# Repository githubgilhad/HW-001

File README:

HW deska pro CPU+RAM+GLUE+SystemBus - prvni navrh

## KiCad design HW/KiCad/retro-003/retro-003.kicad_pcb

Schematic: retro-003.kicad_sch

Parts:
C1, C2: 20p; C_Disc_D5.0mm_W2.5mm_P2.50mm
C12: 100n RESET; C_Disc_D3.0mm_W2.0mm_P2.50mm
Cx6, Cx7, Cx8, Cx9, Cx10, Cx11, Cx12, Cx13, Cx16, Cx17, Cx18: Cx; C_Disc_D3.0mm_W2.0mm_P2.50mm
Cx14, Cx15, Cx27, Cx28: Cx; CP_Radial_D5.0mm_P2.50mm
Cx19, Cx20, Cx21, Cx22, Cx23, Cx24, Cx25, Cx26: 10p; C_Disc_D3.0mm_W2.0mm_P2.50mm
D2: D; D_1210_3225Metric_HandSolder
H5, H6, H7, H8: MountingHole; MountingHole_3.2mm_M3_Pad
J1: ATF_JTAG; IDC-Header_2x05_P2.54mm_Vertical
J2: Conn_02x04_Top_Bottom; PinSocket_2x04_P2.54mm_Vertical
J3: Serial; PinHeader_1x04_P2.54mm_Vertical
J4: SysBus; PinSocket_2x32_P2.54mm_Vertical
J5, J8, J21, J22, J37, J38, J39, J40, J41, J42, J43, J44, J45, J46, J47, J48, J49, J50, J51, J52, J53, J54, J55, J56, J57, J58, J59, J60, J61, J62, J63, J64, J65, J66, J67, J68, J69, J70, J71, J72, J73, J74, J75, J76, J77, J78, J79, J80, J81, J82, J83, J84, J85, J86, J87, J88, J89, J90, J91, J92, J93, J94, J95, J96, J97, J98, J99, J100, J101, J102, J103, J104, J105, J106: x; PinHole_1x01_2.54xrectangle
J6: SysBus; PinHeader_2x32_P2.54mm_Vertical_down
J7: Conn_01x16_Pin; G_SOIC-16_3.9x9.9mm_HandSolder
J12: Reset; PinHole_1x01_2.54xrectangle
JP1: Nx4; SolderJumper-2_P1.3mm_Bridged_Pad1.0x1.5mm
JP2: Nx5; SolderJumper-2_P1.3mm_Bridged_Pad1.0x1.5mm
JP3: Nx6; SolderJumper-2_P1.3mm_Bridged_Pad1.0x1.5mm
JP4: Nx1; SolderJumper-2_P1.3mm_Bridged_Pad1.0x1.5mm
JP5: Nx2; SolderJumper-2_P1.3mm_Bridged_Pad1.0x1.5mm
JP13: Nx3; SolderJumper-2_P1.3mm_Bridged_Pad1.0x1.5mm
Jx1: BugFix; PinHeader_1x03_P2.54mm_Vertical
Jx2: BootFrom; PinHeader_1x03_P2.54mm_Vertical
Jx4: J; PinHeader_1x08_P2.54mm_Vertical
L0: LReset; LED_0805_2012Metric
L1: LHALT; LED_0805_2012Metric
L2: A_HALT; LED_0805_2012Metric
L3: ROM; LED_0805_2012Metric
L4: LRomMapped; LED_0805_2012Metric
L5: B_HALT; LED_0805_2012Metric
L6: MHF_B; LED_0805_2012Metric
L7: MHF_A; LED_0805_2012Metric
L8: RAM; LED_0805_2012Metric
L9: Dev_3; LED_0805_2012Metric
L10: ACIA; LED_0805_2012Metric
L11: VIA; LED_0805_2012Metric
L12: Dev_6; LED_0805_2012Metric
L13: Dev_5; LED_0805_2012Metric
L14: Dev_4; LED_0805_2012Metric
L17: Dev_7; LED_0805_2012Metric
L36: A0; LED_0805_2012Metric
L37, L57: A1; LED_0805_2012Metric
L38, L56: A2; LED_0805_2012Metric
L39: A3; LED_0805_2012Metric
L40: A4; LED_0805_2012Metric
L41: A5; LED_0805_2012Metric
L42: A6; LED_0805_2012Metric
L43: A7; LED_0805_2012Metric
L44: B0; LED_0805_2012Metric
L45, L55: B1; LED_0805_2012Metric
L46, L54: B2; LED_0805_2012Metric
L47: B3; LED_0805_2012Metric
L48: B4; LED_0805_2012Metric
L49: B5; LED_0805_2012Metric
L50: B6; LED_0805_2012Metric
L51: B7; LED_0805_2012Metric
L52: IA; LED_0805_2012Metric
L53: IB; LED_0805_2012Metric
L58: Rx; LED_0805_2012Metric
L59: Tx; LED_0805_2012Metric
LS1: Speaker_Crystal; Buzzer_12x9.5RM7.6
LSys1: Sys; LED_0805_2012Metric
M3: CY7C109D-10ZXI; G_TSOP-I-32_18.4x8mm_HandSolder
PA1: J; PinHeader_1x10_P2.54mm_Vertical
PB1: J; PinHeader_1x10_P2.54mm_Vertical
Q1: MMBT3904; SOT-23
R0, R1, R2, R3, R4, R5, R6, R7, R8, R9, R10, R11, R12, R13, R14, R17, R61, R62, R69, R70, R71, R72, R73, R74, R75, R76, R77, R78, R79, R80, R81, R82, R83, R84, R85, R86, R87, R88, R89, R90, R91, R92: 1k; R_0805_2012Metric_Pad1.20x1.40mm_HandSolder
R36, R37, R38, R39, R44, R45, R46, R47: 5k8; R_0805_2012Metric
R40, R41, R42, R43: 220; R_0805_2012Metric
R48, R49, R50, R51, R52, R53, R54, R55, R56, R57, R58, R59, R64, R95, R96, R98, R99, R100, R102: 10k; R_0805_2012Metric_Pad1.20x1.40mm_HandSolder
R60: 1M; R_0805_2012Metric_Pad1.20x1.40mm_HandSolder
R63: 3k3; R_0805_2012Metric_Pad1.20x1.40mm_HandSolder
R93, R94: 50k; R_0805_2012Metric_Pad1.20x1.40mm_HandSolder
S1: Reset; G_Arduino_switch; PARTREV 1.0
TP1, TP16: 7; TestPoint_Pad_1.0x1.0mm
TP2, TP9: 0; TestPoint_Pad_1.0x1.0mm
TP3, TP10: 1; TestPoint_Pad_1.0x1.0mm
TP4, TP11: 2; TestPoint_Pad_1.0x1.0mm
TP5, TP12: 3; TestPoint_Pad_1.0x1.0mm
TP6, TP13: 4; TestPoint_Pad_1.0x1.0mm
TP7, TP14: 5; TestPoint_Pad_1.0x1.0mm
TP8, TP15: 6; TestPoint_Pad_1.0x1.0mm
TP17: D; TestPoint_Pad_1.0x1.0mm
TP18: Clk; TestPoint_Pad_1.0x1.0mm
TP19, TP36: Q; TestPoint_Pad_1.0x1.0mm
TP20: ~{Q}; TestPoint_Pad_1.0x1.0mm
TP21: ~{R}; TestPoint_Pad_1.0x1.0mm
TP22: ~{S}; TestPoint_Pad_1.0x1.0mm
TP23: N3; TestPoint_Pad_1.0x1.0mm
TP24: N4; TestPoint_Pad_1.0x1.0mm
TP25: N5; TestPoint_Pad_1.0x1.0mm
TP26: N6; TestPoint_Pad_1.0x1.0mm
TP27: ~{N3}; TestPoint_Pad_1.0x1.0mm
TP28: ~{N4}; TestPoint_Pad_1.0x1.0mm
TP29: ~{N5}; TestPoint_Pad_1.0x1.0mm
TP30: ~{N6}; TestPoint_Pad_1.0x1.0mm
TP31: DEV7; TestPoint_Pad_1.0x1.0mm
TP32: DMA; TestPoint_Pad_1.0x1.0mm
TP33: MRDY; TestPoint_Pad_1.0x1.0mm
TP34: BA; TestPoint_Pad_1.0x1.0mm
TP35: BS; TestPoint_Pad_1.0x1.0mm
TP37: N1; TestPoint_Pad_1.0x1.0mm
TP38: N2; TestPoint_Pad_1.0x1.0mm
TP39: ~{N1}; TestPoint_Pad_1.0x1.0mm
TP40: ~{N2}; TestPoint_Pad_1.0x1.0mm
U1: HD6309; DIP-40_W15.24mm
U4: MC68B50; DIP-24_W15.24mm
U5: 6822; DIP-40_W15.24mm
U6, U7, U8: 74HC14; SOIC-14_3.9x8.7mm_P1.27mm
U12: 74HC04; SOIC-14_3.9x8.7mm_P1.27mm
U13: 74HC74; SOIC-14_3.9x8.7mm_P1.27mm
U14: 28C256; DIP-28_W15.24mm
U15: ATF1508AS-10AU100; ATF1508-AS_TQFP100_long
XTAL1: 16MHz; Crystal_HC49-4H_Vertical
Y1: 1.8432 MHz; Crystal_THT_15_5mm

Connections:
+5V: Cx6.1, Cx7.1, Cx8.1, Cx9.1, Cx10.1, Cx11.1, Cx12.1, Cx13.1, Cx14.1, Cx15.1, Cx16.1, Cx17.1, Cx18.1, Cx27.1, Cx28.1, D2.1 (K), J1.4 (Vcc), J2.1, J2.3, J2.5, J2.7, J3.4, J4.1, J4.2, J5.1, J6.1, J6.2, Jx4.8, L6.2 (A), L7.2 (A), LS1.1, LSys1.2 (A), M3.6 (CS2/CE2), M3.8 (VCC), PA1.10, PB1.10, R36.2, R37.2, R38.2, R39.2, R48.2, R49.2, R50.2, R51.2, R52.2, R53.2, R54.2, R55.2, R56.2, R57.2, R58.2, R59.2, R63.1, R64.1, R93.1, R94.1, R95.2, R98.2, R99.2, R100.2, R102.2, U1.7 (VCC), U4.8 (CS0), U4.10 (CS1), U4.12 (VCC), U5.20 (VCC), U5.22 (CS0), U5.24 (CS1), U6.14 (VCC), U7.14 (VCC), U8.14 (VCC), U12.14 (VCC), U13.1 (~R), U13.4 (~S), U13.14 (VCC), U14.28 (VCC), U15.3 (VCCIO), U15.18 (VCCIO), U15.34 (VCCIO), U15.39 (VCCINT), U15.51 (VCCIO), U15.66 (VCCIO), U15.82 (VCCIO), U15.91 (VCCINT)
/A_HALT: J4.29, J6.29, R93.2, U6.1, U15.27 (I/O)
/A_SHARE_DIRTY: J4.33, J6.33, U15.31 (I/O)
/A_SHARE_REQUEST: J4.37, J6.37, U15.36 (I/O)
/A_S_16: J4.27, J6.27, R100.1, U15.24 (I/O)
/B_READ: J4.32, J6.32, U15.30 (I/O)
/B_SHARE_DIRTY: J4.34, J6.34, U15.32 (I/O)
/B_SHARE_REQUEST: J4.38, J6.38, U15.37 (I/O)
/B_SHARE_SELECT: J4.52, J6.52, U15.55 (I/O)
/B_S_16: J4.28, J6.28, R102.1, U15.25 (I/O)
/BootSrc: Jx2.2, U15.84 (I/O)
/CA0: J4.11, J6.11, M3.20 (A0), U1.8 (A0), U4.11 (RS), U5.36 (RS0), U14.10 (A0), U15.5 (I/O)
/CA1: J4.12, J6.12, M3.19 (A1), U1.9 (A1), U5.35 (RS1), U14.9 (A1), U15.6 (I/O)
/CA2: J4.13, J6.13, M3.18 (A2), U1.10 (A2), U14.8 (A2), U15.7 (I/O)
/CA3: J4.14, J6.14, M3.17 (A3), U1.11 (A3), U14.7 (A3), U15.8 (I/O)
/CA4: J4.15, J6.15, M3.16 (A4), U1.12 (A4), U14.6 (A4), U15.9 (I/O)
/CA5: J4.16, J6.16, M3.15 (A5), U1.13 (A5), U14.5 (A5), U15.10 (I/O)
/CA6: J4.17, J6.17, M3.14 (A6), U1.14 (A6), U14.4 (A6), U15.12 (I/O)
/CA7: J4.18, J6.18, M3.13 (A7), U1.15 (A7), U14.3 (A7), U15.13 (I/O)
/CA8: J4.19, J6.19, M3.3 (A8), U1.16 (A8), U14.25 (A8), U15.14 (I/O)
/CA9: J4.20, J6.20, M3.2 (A9), U1.17 (A9), U14.24 (A9), U15.16 (I/O)
/CA10: J4.21, J6.21, M3.31 (A10), U1.18 (A10), U14.21 (A10), U15.17 (I/O)
/CA11: J4.22, J6.22, M3.1 (A11), U1.19 (A11), U14.23 (A11), U15.19 (I/O)
/E: J4.53, J6.53, U1.34 (E), U4.14 (E), U5.25 (ENABLE), U13.3 (C), U15.87 (INPUT/GCLK1)
/GA12: J4.23, J6.23, M3.12 (A12), U14.2 (A12), U15.61 (I/O)
/GA13: J4.24, J6.24, M3.4 (A13), U14.26 (A13), U15.60 (I/O)
/GA14: J4.25, J6.25, M3.11 (A14), U14.1 (A14), U15.58 (I/O)
/GA15: J4.26, J6.26, M3.7 (A15), U15.57 (I/O)
/RomMapped: U6.11, U15.85 (I/O/GCLK3)
/Rx: J3.1, R91.2, U4.2 (Rx_Data)
/R~W: J4.54, J6.54, U1.32 (R/~W), U4.13 (R/~W), U5.21 (R/~W), U15.93 (I/O)
/Tx: J3.2, R92.2, U4.6 (Tx_Data)
/mA_READ: J4.31, J6.31, U15.29 (I/O)
/mA_SHARE_GRANTED: J4.35, J6.35, U7.3, U15.33 (I/O)
/mA_SHARE_SELECT: J4.51, J6.51, U15.54 (I/O)
/mB_HALT: J4.30, J6.30, R94.2, U6.13, U15.28 (I/O)
/mB_SHARE_GRANTED: J4.36, J6.36, U7.1, U15.35 (I/O)
/vCA1: Jx4.1, R90.2, U5.40 (CA1)
/vCA2: Jx4.2, R89.2, U5.39 (CA2)
/vCB1: Jx1.1, Jx4.3, R88.2, U13.2 (D)
/vCB2: Jx4.4, R87.2, U5.19 (CB2)
/v~IRQA: Jx4.5, R86.2, U5.38 (~IRQA)
/v~IRQB: Jx4.6, R85.2, U5.37 (~IRQB)
/~Dev_1: J4.58, J6.58, R55.1, U7.9, U15.70 (I/O)
/~Dev_2: J4.59, J6.59, R56.1, U8.5, U15.71 (I/O)
/~Dev_3: J4.60, J6.60, R57.1, U8.3, U15.72 (I/O)
/~Dev_4: J4.61, J6.61, R58.1, U8.1, U15.75 (I/O)
/~FIRQ: J4.57, J6.57, R50.1, U1.4 (~FIRQ), U15.80 (I/O)
/~IRQ: J4.56, J6.56, R49.1, U1.3 (~IRQ), U4.7 (~IRQ), U15.81 (I/O)
/~NMI: J4.55, J6.55, R48.1, U1.2 (~NMI), U15.83 (I/O)
ACIA Clk 1.8432 MHz: U4.3 (Rx_CLK), U4.4 (Tx_CLK), U12.4
A_G_A_DIR: J4.47, J6.47, U15.49 (I/O)
A_G_D_DIR: J4.49, J6.49, U15.52 (I/O)
A_G_ENABLE: J4.45, J6.45, U15.47 (I/O)
A_S_READ: J4.41, J6.41, U15.42 (I/O)
A_S_SELECT: J4.39, J6.39, U15.40 (I/O)
A_S_WRITE: J4.43, J6.43, U15.45 (I/O)
BA: TP34.1, U1.6 (BA), U15.88 (12V/INPUT/OE1)
BS: TP35.1, U1.5 (BS), U15.77 (I/O)
B_G_A_DIR: J4.48, J6.48, U15.50 (I/O)
B_G_D_DIR: J4.50, J6.50, U15.53 (I/O)
B_G_ENABLE: J4.46, J6.46, U15.48 (I/O)
B_S_READ: J4.42, J6.42, U15.44 (I/O)
B_S_SELECT: J4.40, J6.40, U15.41 (I/O/PD2)
B_S_WRITE: J4.44, J6.44, U15.46 (I/O)
CA12: U1.20 (A12), U15.20 (I/O)
CA13: U1.21 (A13), U15.21 (I/O)
CA14: U1.22 (A14), U15.22 (I/O)
CA15: U1.23 (A15), U15.23 (I/O)
D0: J4.3, J6.3, M3.21 (DQ0), U1.31 (D0), U4.22 (D0), U5.33 (D0), U14.11 (D0), U15.94 (I/O)
D1: J4.4, J6.4, M3.22 (DQ1), U1.30 (D1), U4.21 (D1), U5.32 (D1), U14.12 (D1), U15.96 (I/O)
D2: J4.5, J6.5, M3.23 (DQ2), U1.29 (D2), U4.20 (D2), U5.31 (D2), U14.13 (D2), U15.97 (I/O)
D3: J4.6, J6.6, M3.25 (DQ3), U1.28 (D3), U4.19 (D3), U5.30 (D3), U14.15 (D3), U15.98 (I/O)
D4: J4.7, J6.7, M3.26 (DQ4), U1.27 (D4), U4.18 (D4), U5.29 (D4), U14.16 (D4), U15.99 (I/O)
D5: J4.8, J6.8, M3.27 (DQ5), U1.26 (D5), U4.17 (D5), U5.28 (D5), U14.17 (D5), U15.100 (I/O)
D6: J4.9, J6.9, M3.28 (DQ6), U1.25 (D6), U4.16 (D6), U5.27 (D6), U14.18 (D6), U15.1 (PD1/I/O)
D7: J4.10, J6.10, M3.29 (DQ7), U1.24 (D7), U4.15 (D7), U5.26 (D7), U14.19 (D7), U15.2 (I/O)
GA16: M3.10 (A16), U15.56 (I/O)
GND: C1.1, C2.1, C12.2, Cx6.2, Cx7.2, Cx8.2, Cx9.2, Cx10.2, Cx11.2, Cx12.2, Cx13.2, Cx14.2, Cx15.2, Cx16.2, Cx17.2, Cx18.2, Cx19.2, Cx20.2, Cx21.2, Cx22.2, Cx23.2, Cx24.2, Cx25.2, Cx26.2, Cx27.2, Cx28.2, J1.2 (GND), J1.10 (GND), J2.2, J2.4, J2.6, J2.8, J3.3, J4.63, J4.64, J6.63, J6.64, J8.1, JP1.1 (A), JP2.1 (A), JP3.1 (A), JP4.1 (A), JP5.1 (A), JP13.1 (A), Jx4.7, L0.1 (K), L1.1 (K), L2.1 (K), L3.1 (K), L4.1 (K), L5.1 (K), L8.1 (K), L9.1 (K), L10.1 (K), L11.1 (K), L12.1 (K), L13.1 (K), L14.1 (K), L17.1 (K), L36.1 (K), L37.1 (K), L38.1 (K), L39.1 (K), L40.1 (K), L41.1 (K), L42.1 (K), L43.1 (K), L44.1 (K), L45.1 (K), L46.1 (K), L47.1 (K), L48.1 (K), L49.1 (K), L50.1 (K), L51.1 (K), L52.1 (K), L53.1 (K), L54.1 (K), L55.1 (K), L56.1 (K), L57.1 (K), L58.1 (K), L59.1 (K), M3.24 (GND), PA1.9, PB1.9, Q1.2 (E), R44.1, R45.1, R46.1, R47.1, R62.1, R96.2, S1.3 (K), S1.4 (A), U1.1 (VSS), U4.1 (VSS), U4.23 (~DCD), U4.24 (~CTS), U5.1 (VSS), U6.7 (GND), U7.7 (GND), U8.7 (GND), U12.7 (GND), U13.7 (GND), U14.14 (GND), U15.11 (GND), U15.26 (GND), U15.38 (GND), U15.43 (GND), U15.59 (GND), U15.74 (GND), U15.86 (GND), U15.95 (GND)
JT_TCK: R36.1, R40.1, R44.2, U15.62 (I/O/TCK)
JT_TDI: R39.1, R43.1, R47.2, U15.4 (I/O/TDI)
JT_TDO: R37.1, R41.1, R45.2, U15.73 (I/O/TDO)
JT_TMS: R38.1, R42.1, R46.2, U15.15 (I/O/TMS)
MRDY: R52.1, TP33.1, U1.36 (MRDY), U15.78 (I/O)
MasterReset: C12.1, D2.2 (A), J4.62, J6.62, J12.1, R64.2, S1.1, S1.2, U1.37 (~RESET), U5.34 (~RESET), U6.5, U15.89 (INPUT/GCLR)
unnamed: Cx19.1, Cx20.1, Cx21.1, Cx22.1, R60.1, U12.2, U12.3, Y1.2
unnamed: Cx23.1, Cx24.1, Cx25.1, Cx26.1, R60.2, U12.1, Y1.1
unnamed: J1.1 (TCK), R40.2
unnamed: J1.9 (TDI), R43.2
unnamed: J1.3 (TDO), R41.2
unnamed: J1.5 (TMS), R42.2
unnamed: J7.1, TP2.1
unnamed: J7.2, TP3.1
unnamed: J7.3, TP4.1
unnamed: J7.4, TP5.1
unnamed: J7.5, TP6.1
unnamed: J7.6, TP7.1
unnamed: J7.7, TP8.1
unnamed: J7.8, TP1.1
unnamed: J7.9, TP16.1
unnamed: J7.10, TP15.1
unnamed: J7.11, TP14.1
unnamed: J7.12, TP13.1
unnamed: J7.13, TP12.1
unnamed: J7.14, TP11.1
unnamed: J7.15, TP10.1
unnamed: J7.16, TP9.1
unnamed: JP1.2 (B), TP24.1, U12.9
unnamed: JP2.2 (B), TP25.1, U12.11
unnamed: JP3.2 (B), TP26.1, U12.13
unnamed: JP4.2 (B), TP37.1, U8.11
unnamed: JP5.2 (B), TP38.1, U8.9
unnamed: JP13.2 (B), TP23.1, U12.5
unnamed: Jx1.2, U5.18 (CB1)
unnamed: Jx1.3, U13.5 (Q)
unnamed: Jx2.1, R95.1
unnamed: Jx2.3, R96.1
unnamed: L0.2 (A), R1.1
unnamed: L1.2 (A), R2.1
unnamed: L2.2 (A), R0.1
unnamed: L3.2 (A), R3.1
unnamed: L4.2 (A), R4.1
unnamed: L5.2 (A), R5.1
unnamed: L6.1 (K), R6.1
unnamed: L7.1 (K), R7.1
unnamed: L8.2 (A), R8.1
unnamed: L9.2 (A), R9.1
unnamed: L10.2 (A), R10.1
unnamed: L11.2 (A), R11.1
unnamed: L12.2 (A), R12.1
unnamed: L13.2 (A), R13.1
unnamed: L14.2 (A), R14.1
unnamed: L17.2 (A), R17.1
unnamed: L36.2 (A), R69.1
unnamed: L37.2 (A), R70.1
unnamed: L38.2 (A), R71.1
unnamed: L39.2 (A), R72.1
unnamed: L40.2 (A), R73.1
unnamed: L41.2 (A), R74.1
unnamed: L42.2 (A), R75.1
unnamed: L43.2 (A), R76.1
unnamed: L44.2 (A), R77.1
unnamed: L45.2 (A), R78.1
unnamed: L46.2 (A), R79.1
unnamed: L47.2 (A), R80.1
unnamed: L48.2 (A), R81.1
unnamed: L49.2 (A), R82.1
unnamed: L50.2 (A), R83.1
unnamed: L51.2 (A), R84.1
unnamed: L52.2 (A), R85.1
unnamed: L53.2 (A), R86.1
unnamed: L54.2 (A), R87.1
unnamed: L55.2 (A), R88.1
unnamed: L56.2 (A), R89.1
unnamed: L57.2 (A), R90.1
unnamed: L58.2 (A), R91.1
unnamed: L59.2 (A), R92.1
unnamed: LSys1.1 (K), R62.2
unnamed: PA1.1, R69.2, U5.2 (PA0)
unnamed: PA1.2, R70.2, U5.3 (PA1)
unnamed: PA1.3, R71.2, U5.4 (PA2)
unnamed: PA1.4, R72.2, U5.5 (PA3)
unnamed: PA1.5, R73.2, U5.6 (PA4)
unnamed: PA1.6, R74.2, U5.7 (PA5)
unnamed: PA1.7, R75.2, U5.8 (PA6)
unnamed: PA1.8, R76.2, U5.9 (PA7)
unnamed: PB1.1, R77.2, U5.10 (PB0)
unnamed: PB1.2, R78.2, U5.11 (PB1)
unnamed: PB1.3, R79.2, U5.12 (PB2)
unnamed: PB1.4, R80.2, U5.13 (PB3)
unnamed: PB1.5, R81.2, U5.14 (PB4)
unnamed: PB1.6, R82.2, U5.15 (PB5)
unnamed: PB1.7, R83.2, U5.16 (PB6)
unnamed: PB1.8, R61.1, R84.2, U5.17 (PB7)
unnamed: Q1.1 (B), R61.2
unnamed: LS1.2, Q1.3 (C)
unnamed: R0.2, U6.2
unnamed: R1.2, U6.6
unnamed: R2.2, U6.4
unnamed: R3.2, U6.8
unnamed: R4.2, U6.10
unnamed: R5.2, U6.12
unnamed: R6.2, U7.2
unnamed: R7.2, U7.4
unnamed: R8.2, U7.6
unnamed: R9.2, U7.8
unnamed: R10.2, U7.10
unnamed: R11.2, U7.12
unnamed: R12.2, U8.2
unnamed: R13.2, U8.4
unnamed: R14.2, U8.6
unnamed: R17.2, U8.12
unnamed: TP27.1, U12.6
unnamed: TP28.1, U12.8
unnamed: TP29.1, U12.10
unnamed: TP30.1, U12.12
unnamed: TP39.1, U8.10
unnamed: TP40.1, U8.8
unnamed: C2.2, U1.38 (EXTAL), XTAL1.2
unnamed: C1.2, U1.39 (XTAL), XTAL1.1
unnamed: TP18.1, U13.11 (C)
unnamed: TP17.1, U13.12 (D)
unnamed: TP19.1, U13.9 (Q)
unnamed: TP20.1, U13.8 (~Q)
unnamed: TP21.1, U13.13 (~R)
unnamed: TP22.1, U13.10 (~S)
Q: TP36.1, U1.35 (Q), U15.90 (INPUT/OE2/GCLK2)
~DMA/BREQ: R51.1, TP32.1, U1.33 (~DMA/BREQ), U15.79 (I/O)
~Dev_Sel_1: R53.1, U5.23 (~CS2), U7.13, U15.68 (I/O)
~Dev_Sel_2: R54.1, U4.9 (CS2), U7.11, U15.69 (I/O)
~Dev_Sel_7: R59.1, TP31.1, U8.13, U15.76 (I/O)
~HALT: R63.2, U1.40 (~HALT), U6.3, U15.92 (I/O)
~RAM: M3.30 (~CS1/~CE1), R98.1, U7.5, U15.67 (I/O)
~ROM: R99.1, U6.9, U14.20 (~CS), U15.65 (I/O)
~Read: M3.32 (~OE), U14.22 (~OE), U15.63 (I/O)
~Write: M3.5 (~WE), U14.27 (~WE), U15.64 (I/O)

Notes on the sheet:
~Reset, NMI, IRQ, FIRQ,E,R~{W}
OUT
Dev_0 RAM
5 E, R/~W ~Reset, HALT, BA
I2C style pullup
60+2+2
Dev 0
RAM
PULLUPS
ATF - 1
Dev_Sel_0 = RAM Dev_Sel_1 = OnBoard VIA Dev_Sel_2 = OnBoard ACIA Dev_Sel_3 = Bus_1 Dev_Sel_4 = Bus_2 Dev_Sel_5 = Bus_3 Dev_Sel_6 = Bus_4 Dev_Sel_7 = OnBoard future use
2x MHF-002
Dev X
TESTPOINTS
SYSTEM LEDs
For future use maybe
CONFIG
HD6309
A000..A01F
EMS2 4K
A100..FFFF
RANGE
TYP
Native RAM 32K
9000..9FFF
0001
6 GLUE registers (xxx = regnum)
0000
1xxx
0100
Memory mapped devices (? 15 x 16 B?)
0011
6309 memory regions
EMS1 4K
A020..A0FF
Native RAM ~ ROM 23.75K
0000..7FFF
CONTENT
0010
8000..8FFF

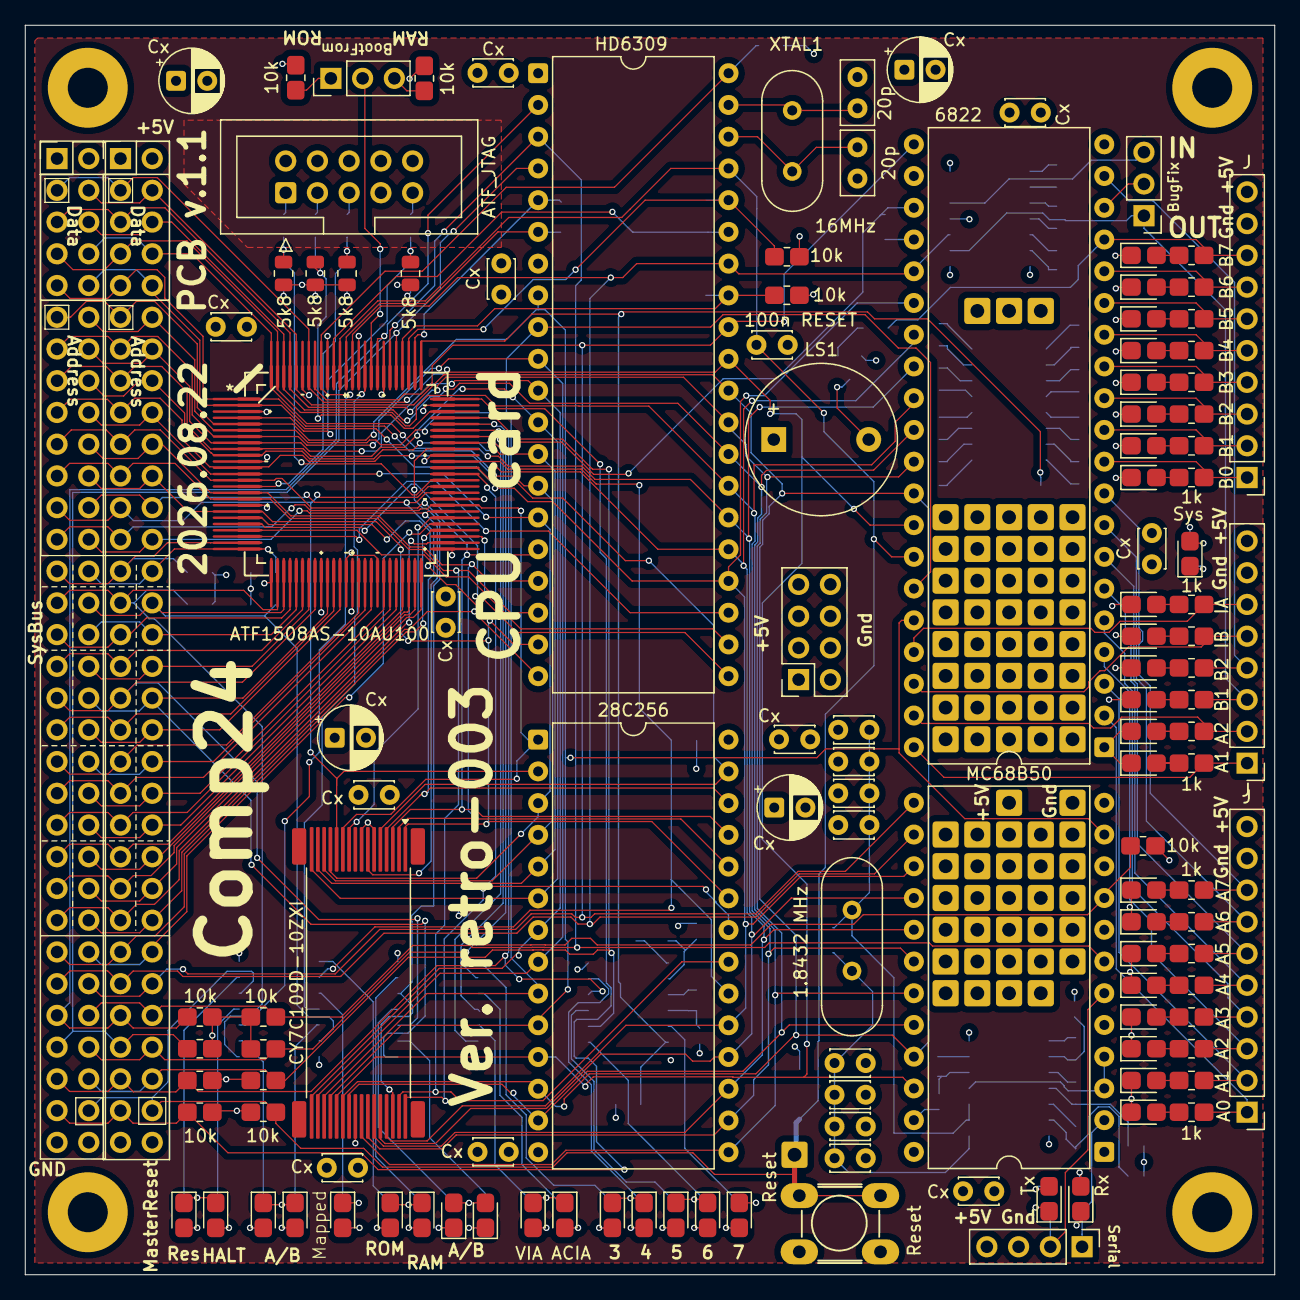
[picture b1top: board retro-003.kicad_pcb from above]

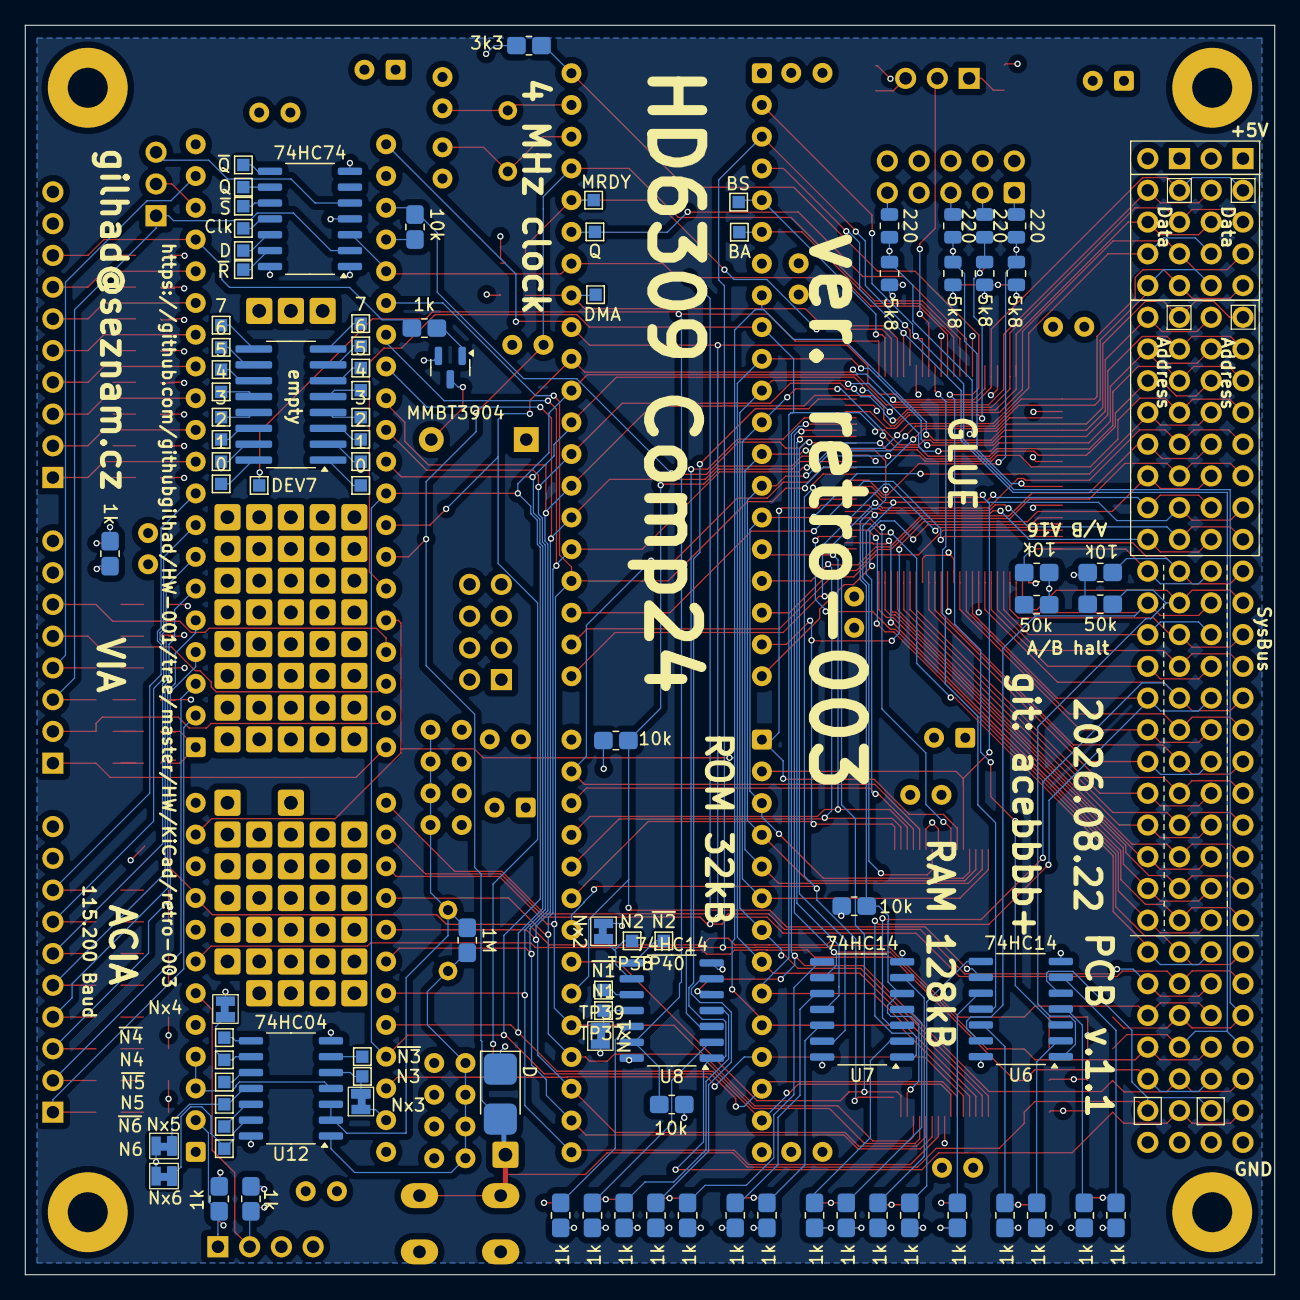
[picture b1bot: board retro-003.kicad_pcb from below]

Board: 4 copper layers, 100.0 x 100.0 mm, 297 parts (92 on the bottom side), 216 nets.
